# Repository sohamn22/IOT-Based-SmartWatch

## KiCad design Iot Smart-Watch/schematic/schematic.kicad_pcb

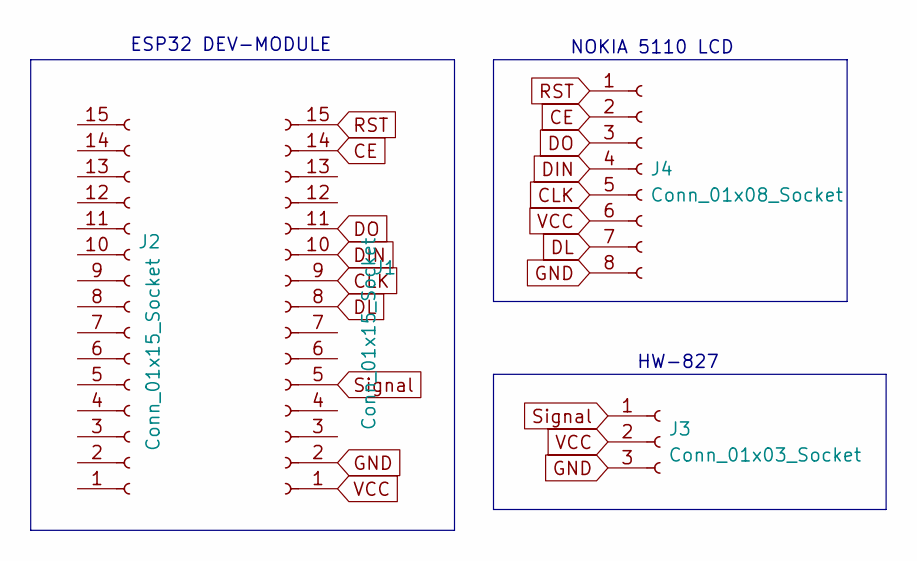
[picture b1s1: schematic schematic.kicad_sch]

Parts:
J1, J2: Conn_01x15_Socket; PinSocket_1x15_P2.54mm_Vertical
J3: Conn_01x03_Socket; PinSocket_1x03_P2.54mm_Vertical
J4: Conn_01x08_Socket; PinSocket_1x08_P2.54mm_Vertical

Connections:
CE: J1.14, J4.2
CLK: J1.9, J4.5
DIN: J1.10, J4.4
DL: J1.8, J4.7
DO: J1.11, J4.3
GND: J1.2, J3.3, J4.8
RST: J1.15, J4.1
Signal: J1.5, J3.1
VCC: J1.1, J3.2, J4.6

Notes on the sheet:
HW-827
NOKIA 5110 LCD
ESP32 DEV-MODULE

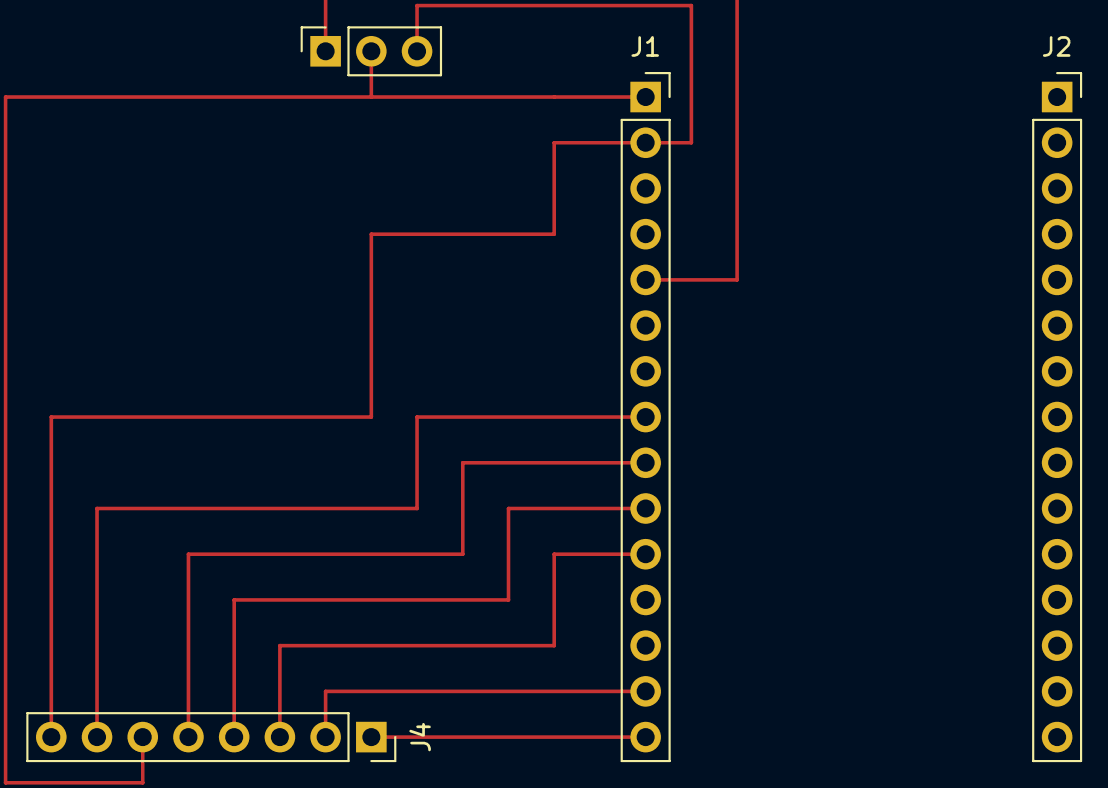
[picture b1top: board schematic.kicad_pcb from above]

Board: 2 copper layers, 4 parts (0 on the bottom side), 9 nets.
